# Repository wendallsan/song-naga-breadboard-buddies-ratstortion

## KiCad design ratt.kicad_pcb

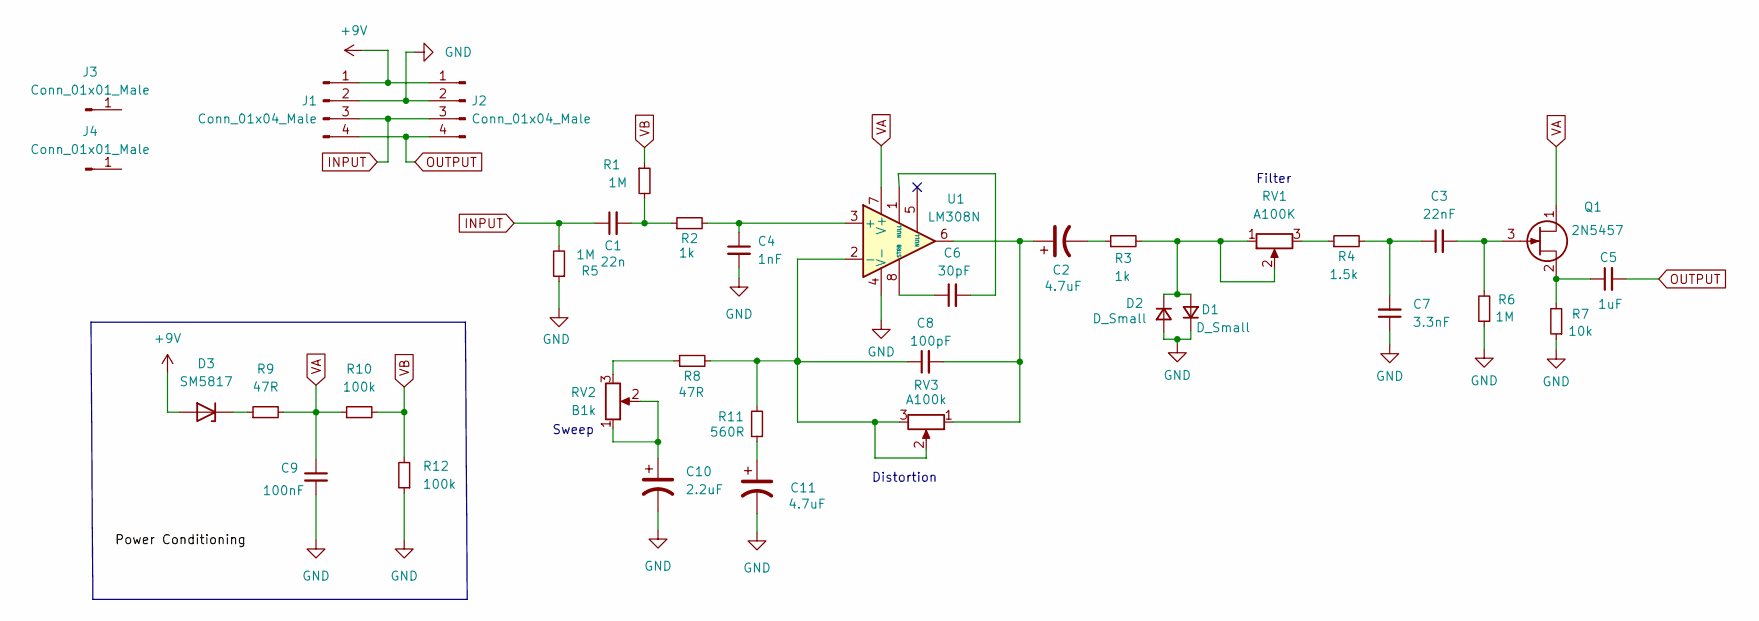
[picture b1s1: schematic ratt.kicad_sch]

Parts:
C1: 22n; C_0805_2012Metric
C2, C11: 4.7uF; C_0805_2012Metric
C3: 22nF; C_0805_2012Metric
C4: 1nF; C_0805_2012Metric
C5: 1uF; C_0805_2012Metric
C6: 30pF; C_0805_2012Metric
C7: 3.3nF; C_0805_2012Metric
C8: 100pF; C_0805_2012Metric
C9: 100nF; C_0805_2012Metric
C10: 2.2uF; C_0805_2012Metric
D1, D2: D_Small; D_MiniMELF
D3: SM5817; D_SOD-123F
J1, J2: Conn_01x04_Male; PinHeader_1x04_P2.54mm_Vertical
J3, J4: Conn_01x01_Male; PinSocket_1x01_P2.54mm_Vertical
Q1: 2N5457; SOT-23
R1, R5, R6: 1M; R_0805_2012Metric
R2, R3: 1k; R_0805_2012Metric
R4: 1.5k; R_0805_2012Metric
R7: 10k; R_0805_2012Metric
R8, R9: 47R; R_0805_2012Metric
R10, R12: 100k; R_0805_2012Metric
R11: 560R; R_0805_2012Metric
RV1: A100K; Potentiometer_Alpha_RD901F-40-00D_Single_Vertical
RV2: B1k; Potentiometer_Alpha_RD901F-40-00D_Single_Vertical
RV3: A100k; Potentiometer_Alpha_RD901F-40-00D_Single_Vertical
U1: LM308N; SOIC-8_3.9x4.9mm_P1.27mm

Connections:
+9V: D3.2 (A), J1.1, J2.1
GND: C4.2, C7.1, C9.2, C10.2, C11.2, D1.1 (K), D2.2 (A), J1.2, J2.2, R5.1, R6.1, R7.1, R12.1, U1.4 (V-)
INPUT: C1.1, J1.3, J2.3, R5.2
unnamed: C1.2, R1.2, R2.1
unnamed: C2.1, C8.2, RV3.1, U1.6
unnamed: C2.2, R3.1
unnamed: C3.1, C7.2, R4.2
unnamed: C3.2, Q1.3 (G), R6.2
unnamed: C4.1, R2.2, U1.3 (+)
unnamed: C5.1, Q1.2 (S), R7.2
unnamed: C6.1, U1.8 (STRB)
unnamed: C6.2, U1.1 (NULL)
unnamed: C8.1, R8.2, R11.2, RV3.2, RV3.3, U1.2 (-)
unnamed: C10.1, RV2.1, RV2.2
unnamed: C11.1, R11.1
unnamed: D1.2 (A), D2.1 (K), R3.2, RV1.1, RV1.2
unnamed: D3.1 (K), R9.1
unnamed: R4.1, RV1.3
unnamed: R8.1, RV2.3
OUTPUT: C5.2, J1.4, J2.4
VA: C9.1, Q1.1 (D), R9.2, R10.1, U1.7 (V+)
VB: R1.1, R10.2, R12.2

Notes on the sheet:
Distortion
Sweep
Filter

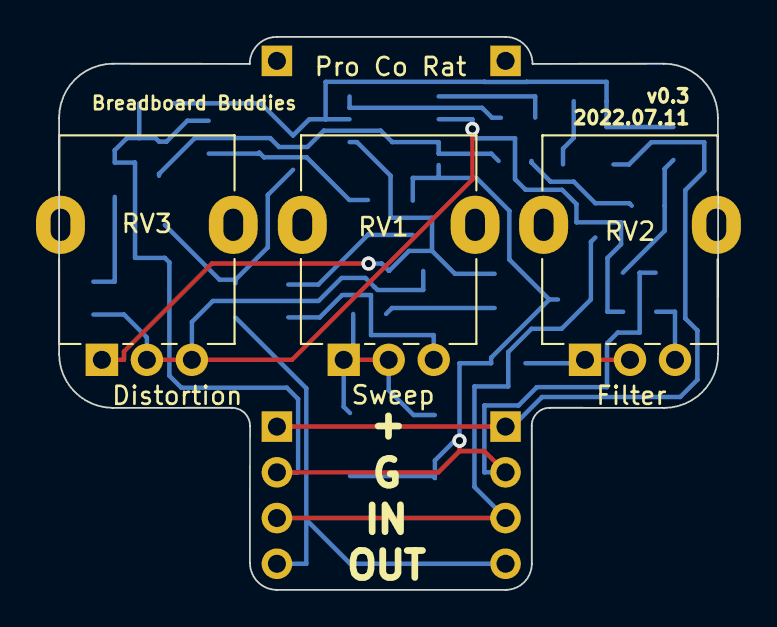
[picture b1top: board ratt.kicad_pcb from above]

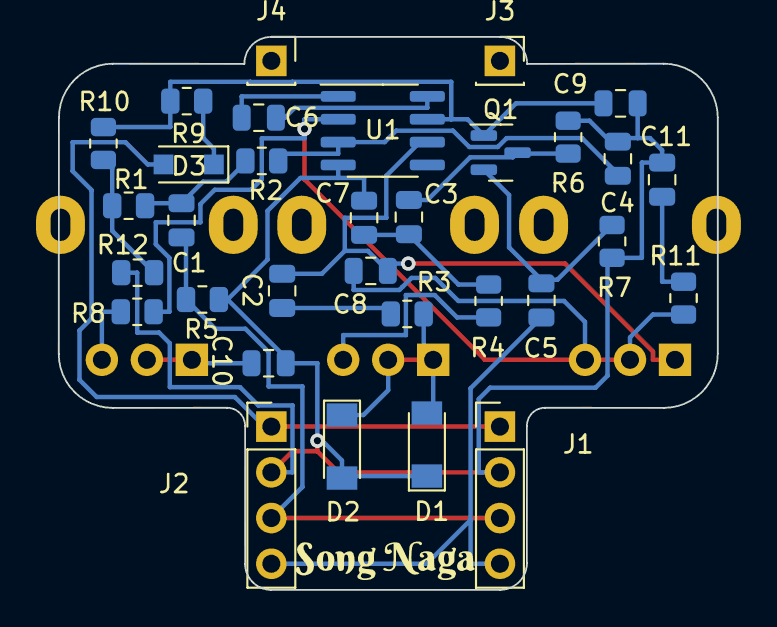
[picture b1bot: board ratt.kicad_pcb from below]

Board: 2 copper layers, 36.6 x 30.7 mm, 36 parts (33 on the bottom side), 22 nets.

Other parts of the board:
G1: LOGO

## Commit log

2022-05-20 initial commit. v0.2 of board, increased the size of the diodes.
2022-07-11 fixed the footprint sizes for diodes.
2022-07-11 updated rotation of pots.
